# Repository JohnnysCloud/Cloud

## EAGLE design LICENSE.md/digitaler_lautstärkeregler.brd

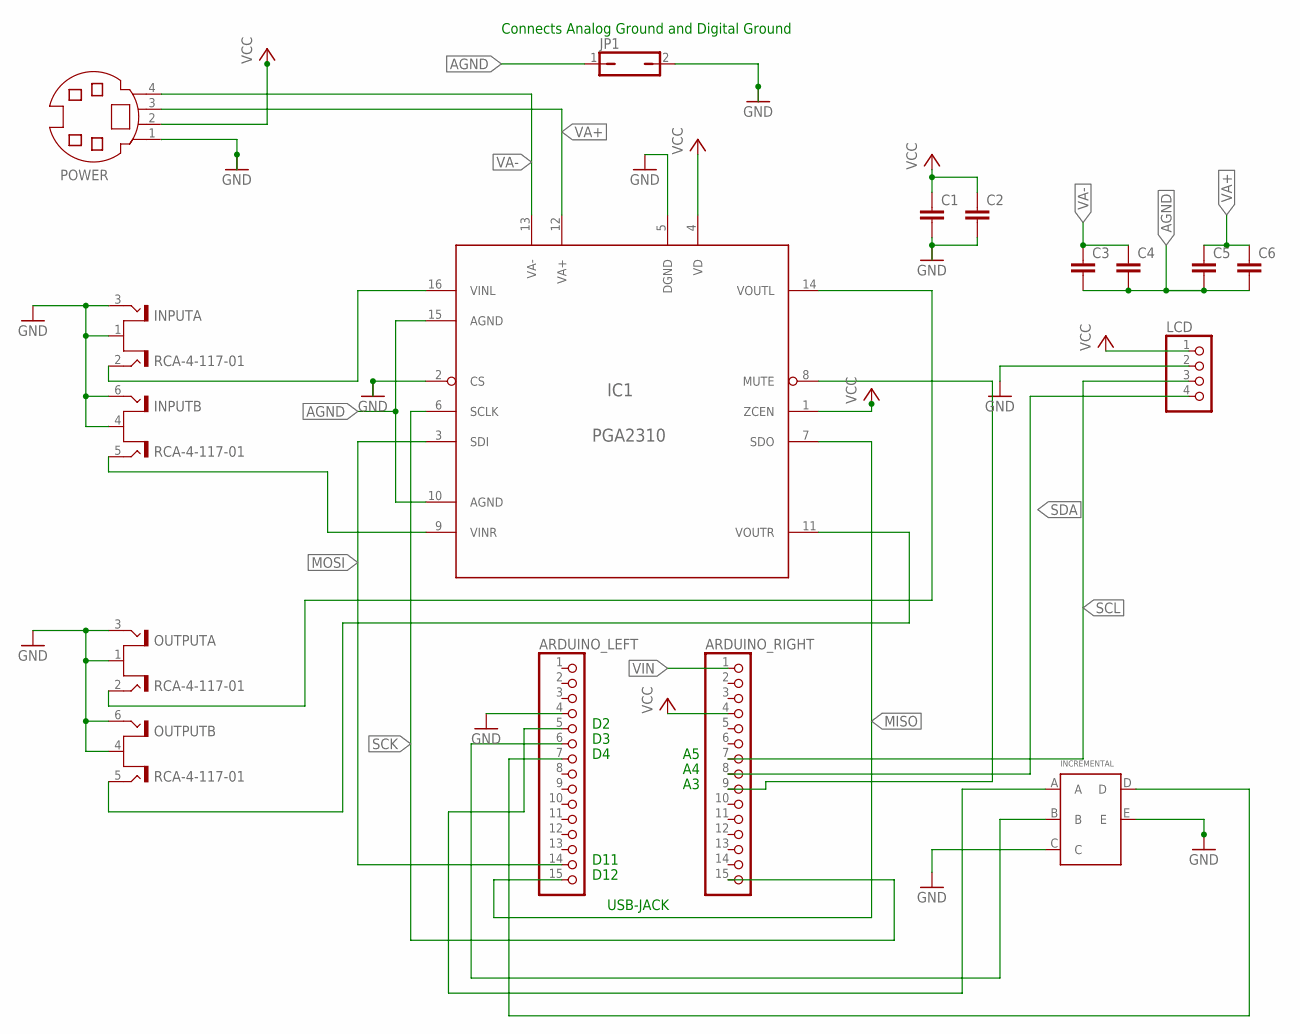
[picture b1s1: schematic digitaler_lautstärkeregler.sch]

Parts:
ARDUINO_LEFT: PINHD-1X15; 1X15
ARDUINO_RIGHT: PINHD-1X15; 1X15
C1, C2, C3, C4, C5, C6: C-EUC1206; C1206
IC1: PGA2310; DIL16
INCREMENTAL: ENCODER
INPUT: RCA-4-117-01
JP1: JP1Q; JP1
LCD: PINHD-1X4; 1X04
OUTPUT: RCA-4-117-01
POWER: MD04S; MDIN04S

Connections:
AGND: C3.2, C4.2, C5.2, C6.2, IC1.10 (AGND), IC1.15 (AGND), JP1.1
GND: ARDUINO_LEFT.4, C1.2, C2.2, IC1.2 (CS), IC1.5 (DGND), INCREMENTAL.C, INCREMENTAL.E, INPUT.1 (S), INPUT.3 (T2), INPUT.4 (S), INPUT.6 (T2), JP1.2, LCD.2, OUTPUT.1 (S), OUTPUT.3 (T2), OUTPUT.4 (S), OUTPUT.6 (T2), POWER.1
LEFTIN: IC1.16 (VINL), INPUT.2 (T1)
LEFTOUT: IC1.14 (VOUTL), OUTPUT.2 (T1)
MISO: ARDUINO_LEFT.15, IC1.7 (SDO)
MOSI: ARDUINO_LEFT.14, IC1.3 (SDI)
unnamed: ARDUINO_RIGHT.9, IC1.8 (MUTE)
unnamed: ARDUINO_LEFT.7, INCREMENTAL.D
unnamed: ARDUINO_LEFT.5, INCREMENTAL.A
unnamed: ARDUINO_LEFT.6, INCREMENTAL.B
RIGHTIN: IC1.9 (VINR)
RIGHTOUT: IC1.11 (VOUTR), OUTPUT.5 (T1)
SCK: ARDUINO_RIGHT.15, IC1.6 (SCLK)
SCL: ARDUINO_RIGHT.7, LCD.3
SDA: ARDUINO_RIGHT.8, LCD.4
VA+: C5.1, C6.1, IC1.12 (VA+), POWER.3
VA-: C3.1, C4.1, IC1.13 (VA-), POWER.4
VCC: ARDUINO_RIGHT.4, C1.1, C2.1, IC1.1 (ZCEN), IC1.4 (VD), LCD.1, POWER.2
VIN: ARDUINO_RIGHT.1

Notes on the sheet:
USB-JACK
Connects Analog Ground and Digital Ground
D11
D12

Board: 2 copper layers, 15 parts (0 on the bottom side), 17 nets, no tracks yet.
